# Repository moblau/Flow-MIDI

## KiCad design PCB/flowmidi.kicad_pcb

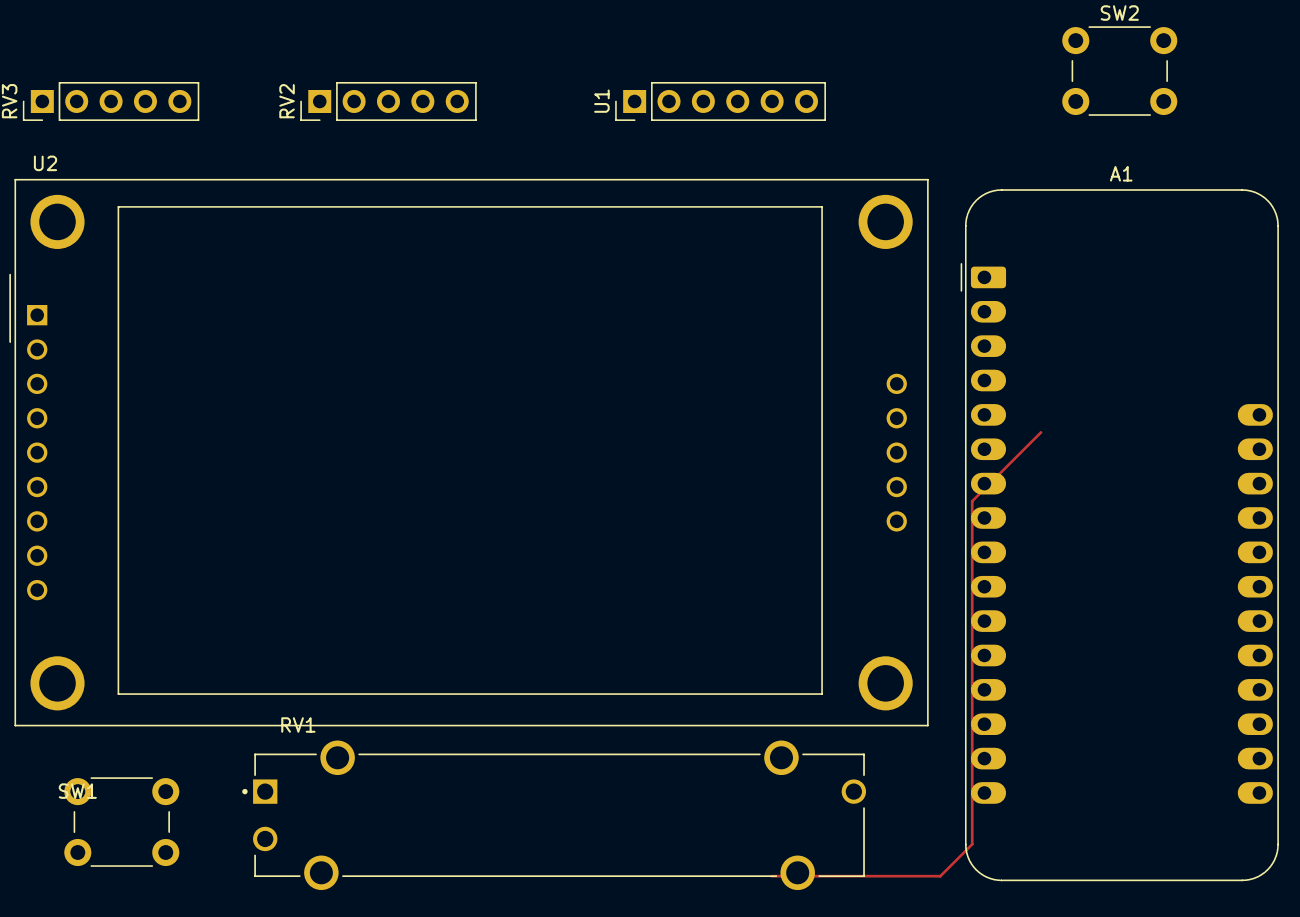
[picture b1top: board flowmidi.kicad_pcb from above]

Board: 2 copper layers, 8 parts (0 on the bottom side), 12 nets.

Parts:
A1: Adafruit_Feather_HUZZAH32_ESP32; Adafruit_Feather
RV1: SP1; TRIM_PTA3043-2010CPB103
RV2: RP1; RP
RV3: RP2; RP
SW1, SW2: Push; SW_PUSH_6mm
U1: VL53L0CXV0DH1; PinHeader_1x06_P2.54mm_Vertical
U2: CR2013-MI2120

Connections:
+3.3V: A1.2 (3V3), RV1.1, RV2.1, RV3.1, U1.1 (AVDDVCSEL), U2.1 (VCC)
GND: A1.4 (GND), RV1.3, RV2.3, RV3.3, SW1.1, U1.3 (GND), U1.4 (GND), U1.6 (GND), U2.2 (GND)
unnamed: A1.19 (A6/IO14), U2.3 (~CS)
unnamed: A1.21 (A8/IO15), U2.5 (D/~C)
unnamed: A1.22 (A9/IO33), U2.4 (RESET)
unnamed: A1.6 (DAC1/A1), RV2.2
unnamed: A1.5 (DAC2/A0), RV1.2
unnamed: A1.7 (I34/A2), RV3.2
unnamed: A1.8 (I39/A3), SW1.2
unnamed: A1.13 (MISO/IO19), U2.9 (MISO), U2.12 (SD_MISO)
unnamed: A1.12 (MOSI/IO18), U2.6 (MOSI), U2.11 (SD_MOSI)
unnamed: A1.11 (SCK/IO5), U2.7 (SCK), U2.13 (SD_SCK)

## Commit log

2025-09-05 init
2025-09-05 adding CC for touchpad, fixed instability
